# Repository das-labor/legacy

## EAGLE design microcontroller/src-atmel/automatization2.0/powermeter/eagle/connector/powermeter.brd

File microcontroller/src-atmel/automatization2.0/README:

This folder contains the current sources of the labor 2.0 house automation project.
If you're looking for labor 1.0 automation sources -> cd ../archive

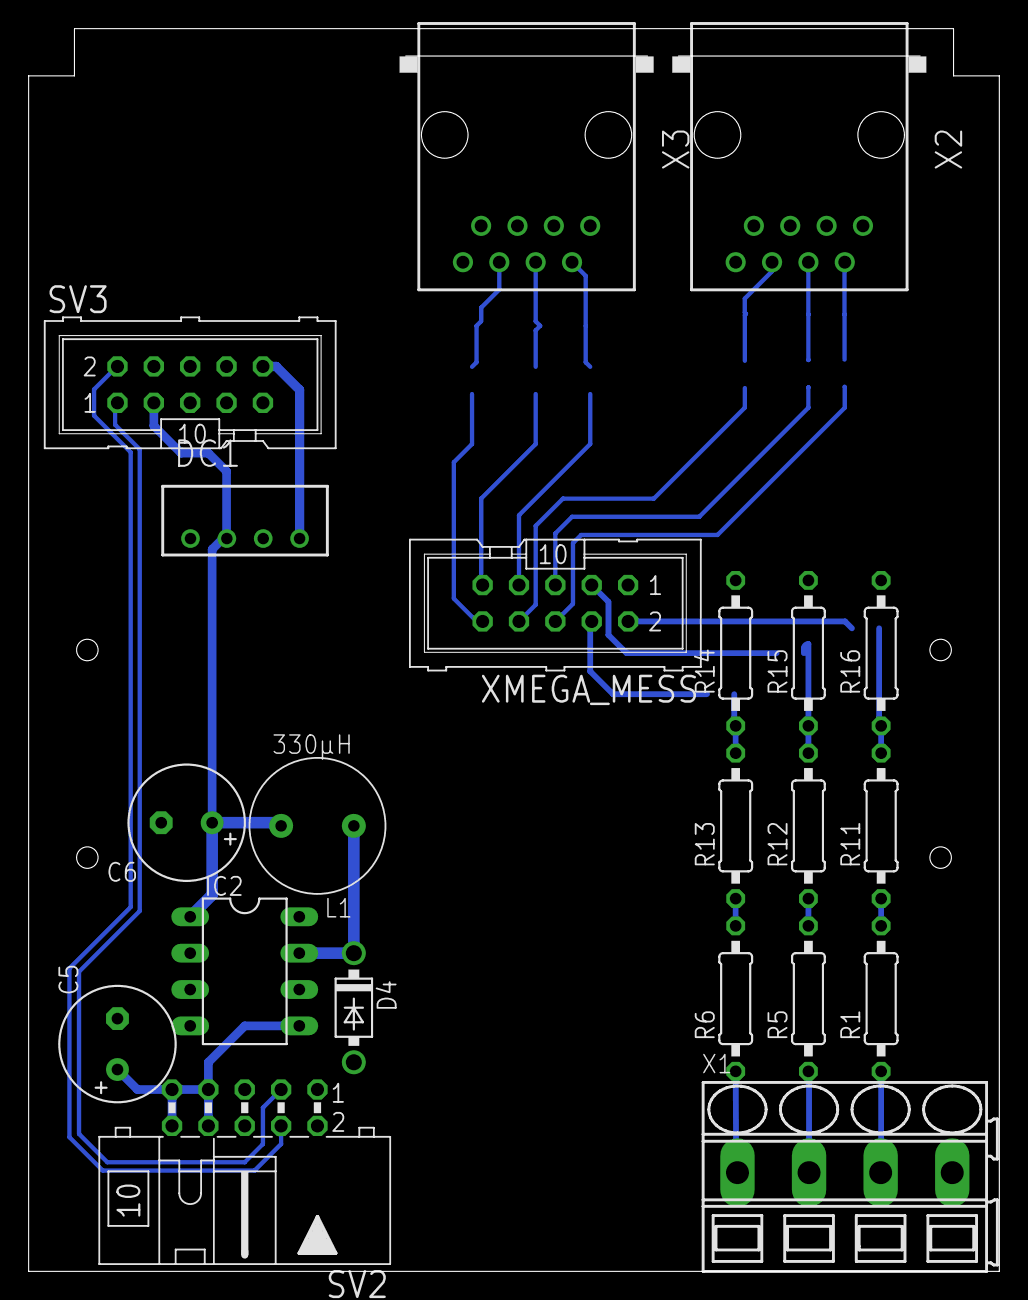
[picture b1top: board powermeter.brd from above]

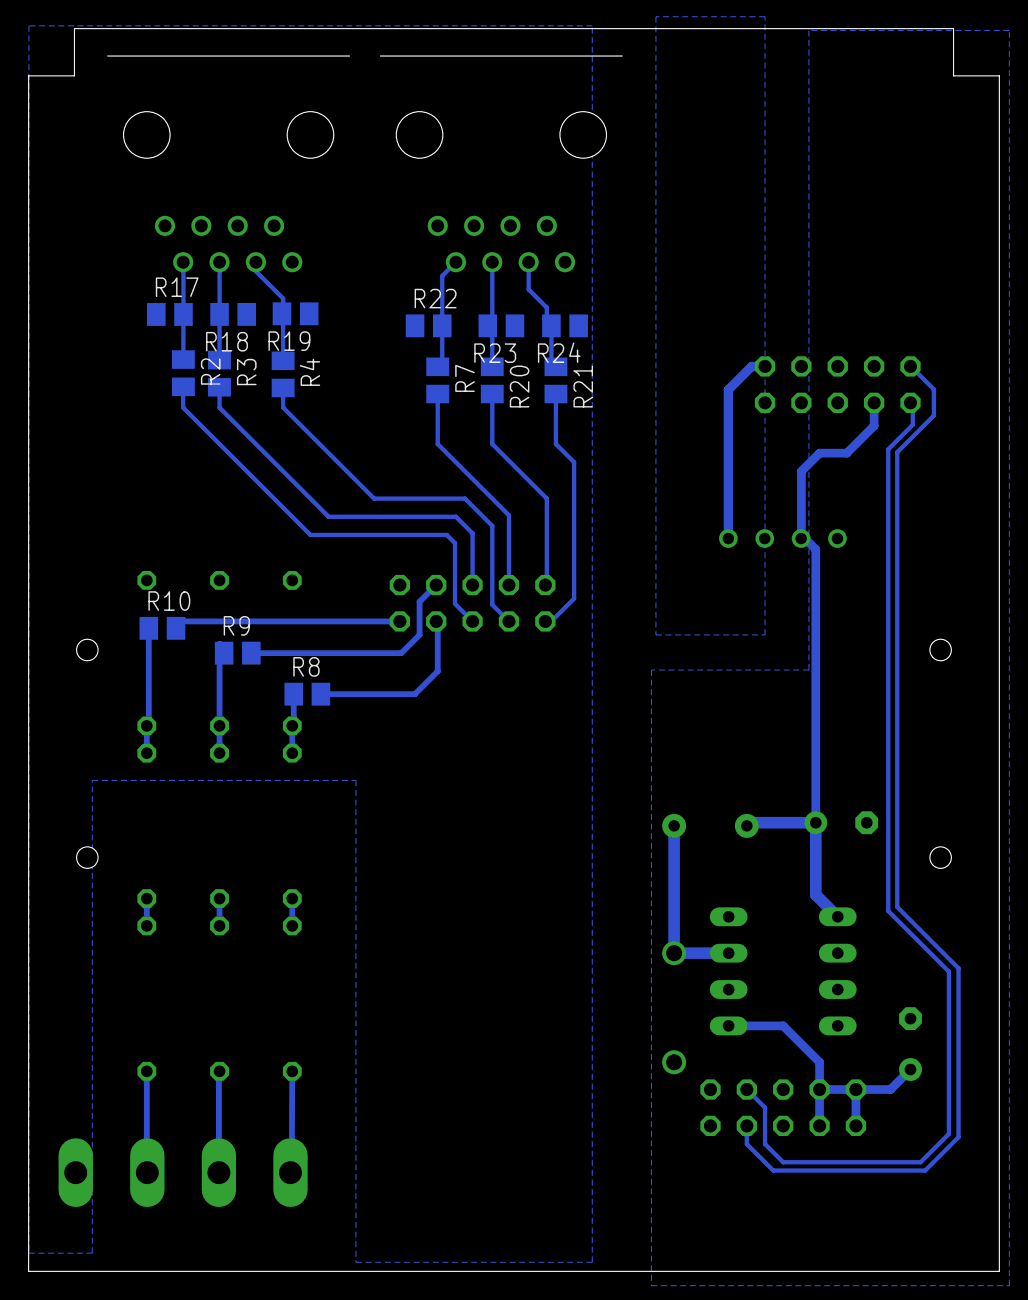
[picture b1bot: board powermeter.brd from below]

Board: 2 copper layers, 67.8 x 86.8 mm, 36 parts (15 on the bottom side), 33 nets.

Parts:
C5: 220µ/35V; E3,5-8
C6: 470µ/10V; E3,5-8
D4: 1N5819; DO41-7
DC1: VA-0505S1.5; 4SIL
IC2: LM2574N-5.0; DIL08
L1: 330µH; FASTRON-09P
R1, R5, R6: 220k; 0207/10
R2, R3, R4, R7, R8, R9, R10, R20, R21: 10k; M0805
R11, R12, R13: 250k; 0207/10
R14, R15, R16: 2k2; 0207/10
R17, R18, R19, R22, R23, R24: 33; M0805
SV2: CAN; ML10L
SV3: XMEGA_P; ML10
X1: SMKDSP_1,5/4
X2, X3: RJ45-8L-S; RJ45-NO-SHIELD
XMEGA_MESS: ML10

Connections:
+5V: C6.+, IC2.1, L1.2, SV3.3
+5V_ISO: DC1.4, SV3.10
+V: C5.+, IC2.5, SV2.7, SV2.8, SV2.9, SV2.10
GND: C5.-, C6.-, D4.A, DC1.1, IC2.2, IC2.3, IC2.4, SV2.1, SV2.2, SV2.5, SV2.6, SV3.4
GND1: DC1.3, SV3.9
unnamed: R10.2, XMEGA_MESS.2
unnamed: R1.2, R11.1
unnamed: R5.2, R12.1
unnamed: R6.2, R13.1
unnamed: R6.1, X1.1
unnamed: R5.1, X1.2
unnamed: R1.1, X1.3
unnamed: R9.2, XMEGA_MESS.3
unnamed: R8.2, XMEGA_MESS.4
unnamed: R7.1, R22.2, X3.2
unnamed: R3.2, XMEGA_MESS.5
unnamed: R8.1, R13.2, R14.1
unnamed: R9.1, R12.2, R15.1
unnamed: R10.1, R11.2, R16.1
unnamed: D4.C, IC2.7, L1.1
unnamed: R4.2, XMEGA_MESS.8
unnamed: SV2.4, SV3.2
unnamed: SV2.3, SV3.1
unnamed: R20.1, R23.2, X3.4
unnamed: R2.2, XMEGA_MESS.6
unnamed: R21.1, R24.2, X3.6
unnamed: R7.2, XMEGA_MESS.7
unnamed: R20.2, XMEGA_MESS.9
unnamed: R21.2, XMEGA_MESS.10
unnamed: R2.1, R17.2, X2.2
unnamed: R3.1, R18.2, X2.4
unnamed: R4.1, R19.2, X2.6
VGND: R14.2, R15.2, R16.2, R17.1, R18.1, R19.1, R22.1, R23.1, R24.1, X1.4, X2.1, X2.3, X2.5, X3.1, X3.3, X3.5, XMEGA_MESS.1

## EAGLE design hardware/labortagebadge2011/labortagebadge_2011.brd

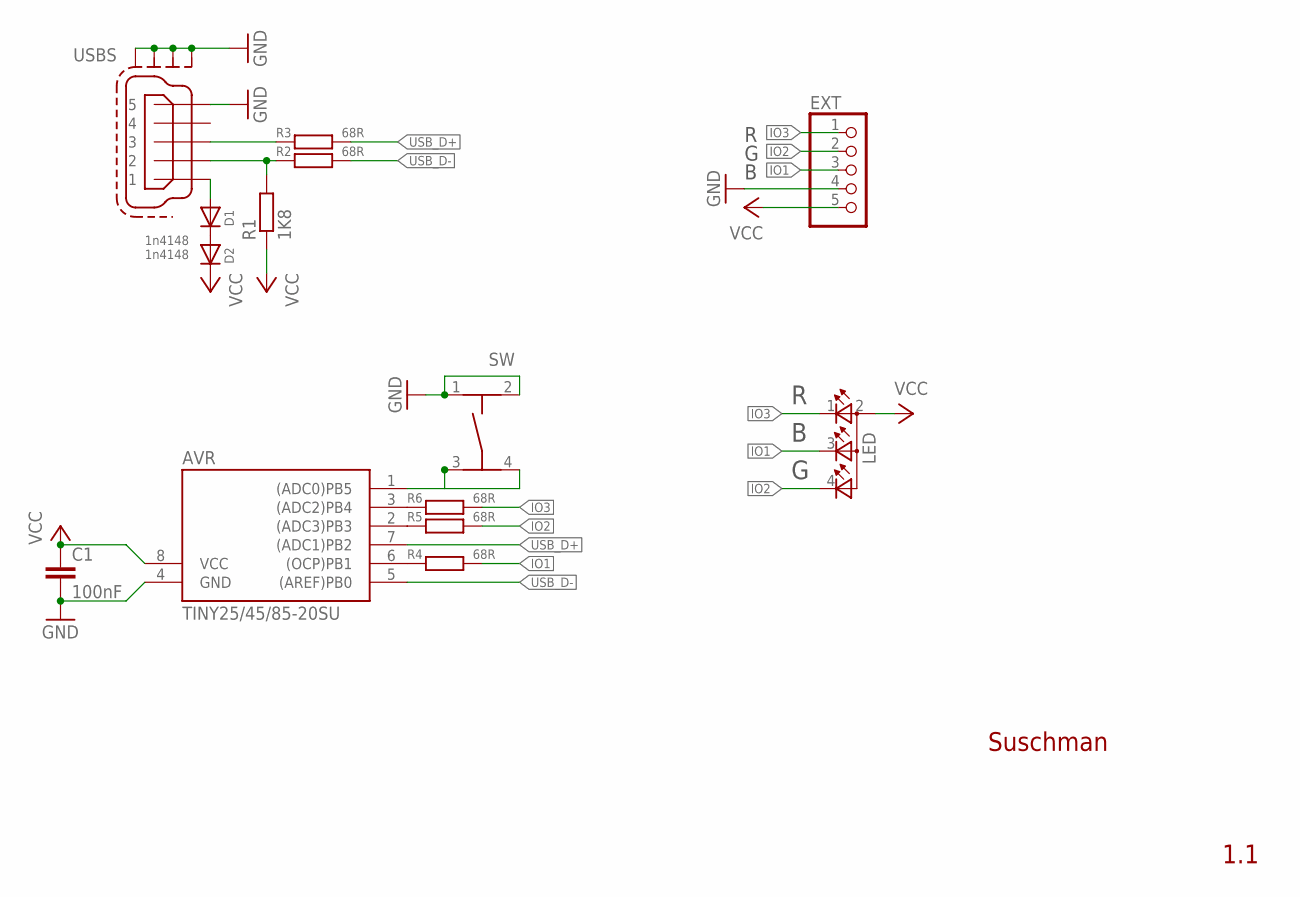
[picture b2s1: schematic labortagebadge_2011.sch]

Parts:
AVR: TINY25/45/85-20SU; SOIC8
C1: 100nF; C0805K
D1, D2: 1n4148; MINIMELF
EXT: PINHD-1X5; 1X05
LED: TOPLED-3; P-LCC-4-3
R1: 1K8; R0805
R2, R3, R4, R5, R6: 68R; R0805
SW: TASTER-9314_SMD
USB: MINI-USB-SCHIELD-32005-201; 32005-201

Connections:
GND: AVR.4 (GND), C1.2, EXT.4, SW.1, SW.2, USB.5, USB.M1 (S1), USB.M2 (S2), USB.M3 (S3), USB.M4 (S4)
IO1: EXT.3, LED.3 (CBLUE), R4.2
IO2: EXT.2, LED.4 (CGREEN), R5.2
IO3: EXT.1, LED.1 (CRED), R6.2
unnamed: AVR.1 ((ADC0)PB5), SW.3, SW.4
unnamed: D1.C, D2.A
unnamed: R1.2, R2.1, USB.2
unnamed: R3.1, USB.3
unnamed: D1.A, USB.1
unnamed: AVR.6 ((OCP)PB1), R4.1
unnamed: AVR.2 ((ADC3)PB3), R5.1
unnamed: AVR.3 ((ADC2)PB4), R6.1
USB_D+: AVR.7 ((ADC1)PB2), R3.2
USB_D-: AVR.5 ((AREF)PB0), R2.2
VCC: AVR.8 (VCC), C1.1, D2.C, EXT.5, LED.2 (A2), R1.1

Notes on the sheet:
Suschman
1.1

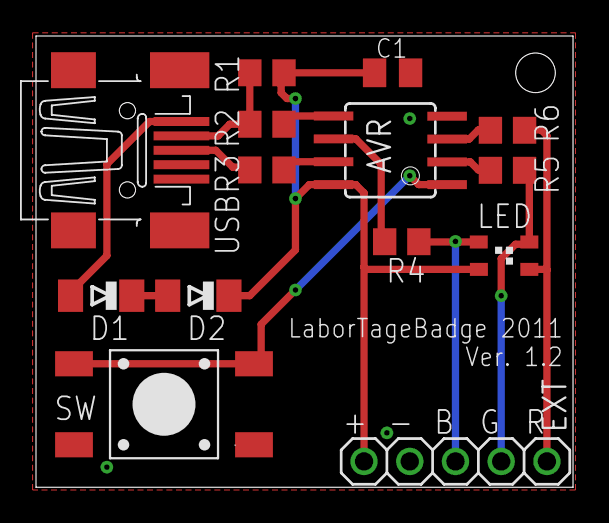
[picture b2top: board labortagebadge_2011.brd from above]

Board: 2 copper layers, 29.8 x 25.1 mm, 14 parts (0 on the bottom side), 15 nets.

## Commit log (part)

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2013-04-14 PC_trunk: can_hander stuff
2013-04-14 kuechencan: no_netvar define for transition
2013-04-14 bugfix, break was missing
2013-04-14 usbPoll() with guaranteed delay -> safer operation
2013-04-15 canboot: cleanup, mcp regs update
2013-04-15 canlib: enum work, add netvar port
2013-04-15 netvar_lib: can_handler update, less magic numbers
2013-04-15 use EEPROM_LAP_ADDR define
2013-04-15 netvar_node:
2013-04-17 treppenblink: wip - animation läuft, netvar_handler killt die animation, buttons nicht ausgewertet
2013-04-21 can_dimmer nv: wip
2013-04-21 kuechencan: no_netvar: wip
2013-04-21 treppenblink: wip support no_netvar
2013-04-22 treppenblink: taster works
2013-05-09 powercommander avr_interface
2013-05-09 kuechencan: fix led stuff, timing taster
2013-05-10 added support for multithreaded asyncronious data input
2013-05-12 added missing files
2013-05-20 fixed mega162 version
2013-05-20 forgot a few files
2013-05-20 bugfix in tx function
2013-05-20 sync
2013-06-02 speed ctrl scrollbar
2013-06-04 foobar
2013-06-06 removed input file support, increased fifo size, wait until fifo has been filled before start drawing stuff
2013-06-07 remove fprintfs, parse --depth and --freq args
2013-06-07 fix fps calculation
2013-06-21 added debug flags, fifo BufferInit returns int instead of void, update usage message
2013-07-14 reduce interrupt time, do not use double buffering, use custom isqrt implementation, use statemachine more efficient, transmit uptime in seconds
2013-07-14 update powermeter_driver to GNU Public License 3
2013-07-17 treppenblink: wip, taster animation wechsel
2013-07-17 kuechencan: build fix, merge ds1631 from treppenblink
2013-07-18 fixed buffer overflow
2013-07-29 use libxrandr to detect all settings
2013-08-01 powermeterd: Fail to flush collectd should not stop us from grawing a graph
2013-08-05 move a free to prevent crash, add error check on file open
2013-08-07 test for flag in dma interrupt and reset interrupt flag by hand
2013-08-13 fix compilation errors
2013-08-13 remove error handler, simplify led driver, cleanup powermeter driver
2013-08-14 always set repeat count and repeat bit
2013-08-15 code cleanup
2013-08-15 add more function
2013-09-14 PowerCommander,trunk,avr_interface: Send input status to bus. statsetter needs it
2013-10-08 treppenblink: fix warnings
2013-10-08 treppenblink: 12 bit LUT im flash - programme nutzen 8 bit farben
2013-10-08 treppenblink: 8 bit farben
2013-10-08 treppenblink: add lap support, use lap addr from makefile webinterface kann animationsmodi wieder ansteuern
2013-10-09 PowerCommander,trunk,avr_interface: fix uninitialised dest addr & port
2013-11-07 rewrite in C, remove C++ code, some bug fixes
2013-11-29 PowerCommander,trunk,avr_interface: change compiler flags, fix warnings, add feedback for vortrag main channel
2013-11-30 cvstatr: merge changes form other projects
2013-12-01 the MCLR pins of the 74HCT164 chips are not connected on Borg 16
2013-12-01 small refinements, slightly fewer cpu utilization in Win32 simulator
2013-12-01 corrected some doxygen tag errors
2013-12-01 kuechencan: merge stuff form other projects, enable temperature readings, use can interrupts, set reg button led from powercommander feedback
2013-12-01 cvstatr: cleanup
2013-12-01 netvar: fix warings with -Wstrict-prototypes
2013-12-01 treppenblink: merge stuff form other projects, enable temperature read, set rgb button led from powercommander feedback
2013-12-01 PowerCommander,trunk,avr_interface: merge stuff form other projects, cleanup
2013-12-01 can: silence warnings
2013-12-01 lapnode,can_dimmer: merge stuff form other projects, cleanup, interrupt support
2013-12-01 bastelraum: merge stuff form other projects, cleanup, interrupt support, switch + leds at the door com via uart
2013-12-03 bastelraum: fixes
2013-12-05 bastelraum: taster code
2013-12-14 PowerCommander,trunk,avr_interface: fix kuechen dim, cleanup
2013-12-18 fix autoreport timeout
2013-12-22 cvstatr controll: fix addr in makefile, cleanup, rote led zeigt sofort das labor aus geht, temperatur seltener senden, code aus anderen projekten, besseres ds1631 default
2013-12-23 PowerCommander,trunk,avr_interface: fix bitmask, cleanup
2013-12-23 PowerCommander,trunk,avr_interface: cleanup, replace bitfields
2013-12-23 PowerCommander,trunk,avr_interface: avoid redundant lamp control code - use structures
2013-12-23 kuechen_can: ds1631 - replace ugly define
2013-12-23 PowerCommander,trunk,avr_interface: fix wrong struct init order, ...
2013-12-25 PowerCommander,trunk,avr_interface: fix empty pwmvals for lounge
2013-12-25 PowerCommander,trunk,avr_interface: replace if - else if with switch, add set_output
2014-01-03 cvstatr: build fixes, better led status display
2014-01-03 powercommander avr_control: small changes, rename stuff
2014-01-03 can-ir: makefile changes form other projects, static vars and functions
2014-01-03 netvar_node: fixes, cleanup
2014-01-03 can_dimmer-netvar: wip
2014-01-03 lapnode can_gateway uart: fix api, cleanup
2014-01-03 lapnode can_gateway: fix api, cleanup
2014-01-03 lcd_touchscreen: main-controller: mcp api fix, format
2014-01-03 labnode can_dimmer: cleanup
2014-01-03 labcontrol: fix some warnings
2014-01-03 labcontrol: replace empty include files
2014-01-03 canlib: less magic
2014-01-03 treppenblink: ds1631 use define
2014-01-03 treppenblink: vorbereitung auf andere taster auswertung, status der animation senden, temperatur seltener senden
2014-01-03 kuechencan: vorbereitung auf andere taster auswertung, cleanup
2014-01-03 powercommander_netvar: use define
2014-01-03 powercommander: send output status, fix bug in last change
2014-01-03 cand_netvar: use new debug api
2014-01-03 cand: use new debug api
2014-01-03 cand: remove include murks
2014-01-03 lapcontrol: fix build
2014-01-17 move gamma correction to dimmer.c, fix status packets
2014-01-17 HACK: switch lounge relais before sending out CAN-packets, the returned status packets are ignored. TODO: find out why!
2014-01-17 powercommander avr_interface: remove hack - fix is in labnode dimmer, powercommander read only staus unaddressed status packets
2014-01-17 labnode can_dimmer: send status without dest addr
2014-02-04 Chnaged image name back to "borg". Added borg.hex to svn
2014-02-04 kuechencan: fix temp reading
2014-02-04 cvstatr: fix temp sensor
2014-02-04 treppenblink: fix temp sensor
2014-02-09 labcontrol: check for real ping answer packet, not any packet form the same address is a pong
2014-02-11 cand: merge stuff from branch, silence warings
2014-02-23 bastelcmd: fix wrong pwm channel return value, cleanup
2014-02-23 powercmd interface: let beamer relay cmds pass
2014-02-23 powercmd interface: allow only power on beamer
2014-03-06 cand_netvar: cleanup, build fixes
2014-03-10 labnode-can_dimmer: remove legacy code
2014-03-10 libcan: add option to reduce cpu cycles needed in message_fetch() and message_load() - results in less interrupt code
2014-03-10 can_dimmer: use faster can int
2014-03-19 make it possible to center multi line strings
2014-03-20 Old and busted!
2014-03-20 old and busted improved
2014-12-06 can-ir: add support for serial beamer controll and i2c sound controll
2014-12-06 labcontroll: codestyle; fix double free; add gw reset, print error flags
2014-12-06 cand_netvar: make baudrate configurable
2014-12-06 cand: make baudrate configurable, move to usblib-1.0, move configure script
2014-12-06 uart lib: fix compile warning
2014-12-06 labnode can_gateway: formating
2014-12-06 canlib:
2014-12-07 implement reset, fix reset cause, add gpio led blink
2014-12-07 canlib: add optimized lap_to_packet func
2014-12-07 bastelraum: fix taster delay
2014-12-07 canboot_lib: use .avrduderc for programmer config
2014-12-07 treppenblink: minor changes
2014-12-07 can-ir: add svn external twi_master
2014-12-07 kuechencan_nofemto: minor changes
2014-12-07 cvstatr_controll: minor changes
2014-12-07 labnode cangw uart: sync to can_gw
2014-12-07 can_gw: sync to labnode
2014-12-07 cand: minor cleanup
2014-12-07 cand_netvar: sync to cand
2014-12-07 add baudrate option
2014-12-07 cand: sync to cand_netvar
2014-12-07 labnode: can_gw sync
2014-12-07 can_dimmer: cs
2014-12-07 canlib: remove exidently merged dev code
2014-12-11 can-ir: wip
2015-01-31 can-ir: disable IR code, add timer
2015-01-31 can-ir: add documentation, fix bug in writeChannel, change default volume
2015-02-01 kuechencan: hardware changed - temp sensor id is 0x92 now
2015-02-02 Zurücksenden von der Lautstärke und verschiedenes
2015-02-02 can-ir: implement wiriteAll, keep default volumes, implement setAllChannels
2015-02-02 Incremental and Mute Mode
2015-02-04 PowerCommander interface: can-ir kann beamer schalten, die gruppenfunktionen für protokoll 2 sind nicht wie gedacht und schalten in der küche das licht ab
2015-02-04 can-ir: beamer abschalt logik wip
2015-02-05 labcontrol: rename configure.in to configure.ac
2015-02-07 can-ir: refactor code, move can_handler to seperate file as in other projects, maybe fix mute and diff bug
2015-02-08 Removed dependencies from the number of channels
2015-02-13 can-ir: wip call beamer_start_shutdown()
2015-02-15 can-ir: wip use correct command
2015-02-16 can-ir: wip seems to work
2015-02-17 can-ir: cleanup
2015-02-23 can-ir: replace dvu with hdmi command, save some memory?, wip
2015-03-04 uartlib: fix codestyle , comments
2015-03-04 uartlib: add support for stdio redirection
2015-03-05 lapcontrol: add filter support for packet dump
2015-03-05 can-ir: get status at reset
2015-03-16 can-ir: optimize can handler
2015-03-16 PowerCommander: minor optimisations
2015-03-17 PowerCommander: only send data on new state
2015-03-19 can-ir: update comments
2015-03-19 can-ir: refactor rs232 send code, support menu buttons, fix cool down detection - untested
2015-03-27 typo, still old and busted!
2015-03-29 fix order of cmds, fix pgmread - no known bugs
2015-03-29 can-ir: fix poweroff
2015-05-20 bugfixes in canir
2015-06-06 can-ir: small fixes
2015-06-06 can-ir: add i2c audio matrix wip
2015-06-07 can-ir: use prama once
2015-06-07 can-ir: audio_matrix wip
2015-06-07 PowerCommander interface: fix lap port on send light switch lounge
2015-06-07 cvstatr: check for dest id of powercmd packets
2015-07-21 can-ir: audio_matrix: fix most bugs, add can interface
2015-08-23 can-ir: fix bugs, disable led blink while off, delay init, reinit after poweron
2015-08-24 can-ir: add interface for webui
2016-05-06 compatibilty for ATMegaXX4 MCUs
2016-05-06 compatibility for ATMegaXX4 MCUs
2016-05-06 set ATmega32 as default again
2016-07-26 added SVG file of a Borg16 sneeze guard (for use with a laser cutter)
2016-08-30 Add tool to import svn externals.
2016-08-30 Add empty directories.
2016-08-30 Add links for former svn externals.
2020-02-11 treppen_blink: update femtoos to 0.922
2020-02-11 treppen_blink: fix femtoos ATmega8 device file
2020-02-11 treppen_blink: add const modifier to femtoos structures where necessary
2020-02-11 treppen_blink: update config for femtoos 0.922
2020-02-11 treppen_blink: remove femtoos parameter which disappeared in avr-gcc some time ago
2020-02-11 treppen_blink: add const where necessary
2020-02-11 treppen_blink: document FEMTOOS_AVR_TOOLDIR
2020-02-11 treppen_blink: clean properly
2020-02-11 treppen_blink: disable and exclude TWIM related code. it spams CAN when there is no temperature sensor attached
2024-07-03 can-ir: fix i2c enums
